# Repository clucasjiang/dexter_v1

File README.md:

# Dexter — Six-Axis Robotic Arm

Dexter is a six-degree-of-freedom robotic arm with a force-controlled gripper, a **PETG-CF 3D-printed structure**, custom controller electronics, and embedded C firmware. The project brings together mechanical design, PCB design, motor communications, and feedback control—from an early prototype to a fully assembled arm that can hold an egg without breaking it.

I designed, built, assembled, programmed, and tested Dexter independently. The stepper-driven arm and the firmware in this repository are the completed, tested first version of an ongoing robotics project. I am now developing a second version with BLDC motors to improve motion quality, control performance, and overall results.

**Core technologies:** KiCad · STM32H562 · Embedded C · RS485 · PID control · Motor current feedback

## Demonstrations

| Gentle grasping | Arm motion |
| --- | --- |
|  |  |
| A PID force loop regulates the grip to hold an egg without breaking it. | A wave demonstration shows the assembled arm in motion. |

The egg demonstration highlights the central controls challenge: applying enough force to retain a delicate object while limiting additional closing motion after contact.

## Mechanical Design

| Early prototype | Fully assembled arm |
| --- | --- |
|  |  |
| An early build used to develop the mechanical arrangement. | The completed assembly integrates the joints, housings, wiring, and gripper. |

- **Printed structure:** PETG-CF (carbon-fiber-filled PETG) forms the arm's structural parts and housings, with metal motors, reducers, bearings, and fasteners integrated into the assembly.
- **Six articulated joints plus a gripper:** Seven addressed motor axes separate arm positioning from grasp-force control.
- **Harmonic reduction:** Reducers transmit motor motion to the joints. J1–J3 use 42 mm motors with 50:1 reduction, and J4–J6 use 35 mm motors with 30:1 reduction.
- **Internal belt-and-pulley transmission:** Belts transfer motion within the links, allowing motors and transmission components to fit inside the printed structure.
- **Portable mechanical deliverable:** The [Dexter STEP assembly](CAD/DexterAssembly.STEP) can be inspected in standard CAD tools.

*Inside the housings: stepper motors, harmonic reduction, and the pulley structure that drives the arm.*

## Electronics

The [KiCad controller project](PCB/main_controller/dexter_pcb.kicad_pro) includes the schematic, PCB layout, component libraries, footprints, and 3D models.

The stepper motors have built-in drivers from **ZDT**, so the STM32 can send movement commands directly over RS485 and read back position, speed, and motor current. Each motor has its own address on the bus.

| Subsystem | Implementation |
| --- | --- |
| Main controller | STM32H562 microcontroller running the arm application and peripheral interfaces. |
| Power | 24 V input through an XT60 connector and an AP63203 regulator for the 3.3 V logic supply. |
| Motor bus | MAX3485 RS485 transceiver; firmware addresses joints as 1–6 and the gripper as 7 at 115200 baud. |
| Grip feedback | The claw motor's built-in phase-current feedback, read over RS485 in milliamps and used as a proxy for grip load. |
| Development interfaces | Debug/programming connections, reset/boot circuitry, and a serial command console. |
| External stop input | PC13 accepts a normally closed emergency-stop loop; an open input requests a stop. This connection is external to the current controller PCB. |

The firmware pin assignments match the controller PCB: PA0/PA1 carry the UART4 motor bus, PA2 controls the MAX3485 transmit enable, and PB5/PB6 provide the UART5 serial console.

## Firmware and Control

The firmware uses a bare-metal C11 application with separate board, protocol, joint-control, gripper-control, and scheduling layers.

### Joint motion and motor feedback

[arm.c](Firmware/App/Src/arm.c) converts joint angles and speeds into motor commands using each joint's reduction and direction. It supports absolute joint moves, configurable travel and speed limits, manual reference capture, explicit arming, and individual or whole-arm stops. Feedback monitoring checks following error, lack of progress, motion deadlines, stale telemetry, and driver faults.

[zdt.c](Firmware/App/Src/zdt.c) implements the ZDT **X-firmware** protocol over RS485, including trapezoidal position moves, current-limited commands, configuration checks, and telemetry decoding. Transactions validate reply framing and acknowledgements, use bounded timeouts, and avoid automatic motion retries. Decoded feedback includes position, speed, following error, current, voltage, temperature, and driver status.

### Force-controlled gripper

[gripper.c](Firmware/App/Src/gripper.c) uses the claw stepper's built-in phase-current feedback as a proxy for grip load. The application polls aggregate status from motor 7 every 20 ms, obtaining current, position, speed, and driver flags together.

The outer PID turns measured phase current into small opening or closing corrections:

1. Ramp the current target gradually to soften initial contact.
2. Filter measured current and its derivative to reduce noise.
3. Apply PID control with derivative on measurement, integral anti-windup, and a current deadband.
4. Accumulate small corrections at the drive's 0.1° resolution, with a maximum requested step of 0.2°.
5. Wait for fresh motor feedback and completion of the previous move before issuing another correction. If a closing step reaches the requested load while stationary before its endpoint, stop the remaining step and read feedback again so the loop can hold or release.

The application dispatches finite, current-limited position moves (`0xCD`), using the drive's internal control loops. Unfiltered current limits, reply freshness, and gripper travel checks remain active while a move is pending. Communication errors, driver faults, or loss of the claw's volatile reference marker stop operation. The installed motors run **X firmware in closed-loop mode**.

Current is a proxy for motor torque and grip load, not a calibrated jaw-force measurement in newtons. Friction, jaw geometry, and direction affect the relationship. `GRIP` takes **milliamps**. The tested configuration uses a 100 mA maximum target, 150 mA drive limit/software trip, 40 mA/s target ramp, and 3 mA deadband. These limits and the PID gains are used by the completed stepper-driven arm, including the gentle grasping demonstration above. Limits live in [robot_config.h](Firmware/App/Inc/robot_config.h), and PID defaults in [gripper.c](Firmware/App/Src/gripper.c).

### Scheduling, diagnostics, and fault handling

- **100 Hz application scheduling target:** Late updates skip missed releases. Blocking motor transactions affect the achieved rate; one arm joint is polled per update.
- **At most 50 Hz PID corrections:** A 20 ms minimum interval, fresh samples, and motor completion determine the actual correction rate.
- **500 ms nominal independent watchdog:** Refreshed only after a completed application update. Startup requests motor stops and leaves motion disarmed.
- **Observable runtime:** `STATUS` reports joint positions and targets, claw phase current and target in mA, feedback validity and age, faults, measured loop frequency, missed releases, longest update, and watchdog-reset status.
- **Buffered serial console:** Interrupt-driven receive/transmit queues keep console traffic separate from command processing; damaged or oversized input lines are discarded.

Current application motion is joint-space control with manual referencing; Cartesian inverse kinematics, automatic homing, and coordinated trajectory planning are not implemented.

## Build and Explore

Start with the [Dexter STEP assembly](CAD/DexterAssembly.STEP) for the mechanism, the [KiCad schematic](PCB/main_controller/dexter_pcb.kicad_sch) for electronics, and [robot_app.c](Firmware/App/Src/robot_app.c) for application behavior.

### Build the firmware

Requires CMake 3.22+, Ninja, and the GNU Arm Embedded toolchain (`arm-none-eabi-*`) on `PATH`. From the repository root:

```sh
cd Firmware
cmake --preset Debug
cmake --build --preset Debug
```

Outputs are `build/Debug/dexter_legacy.elf`, `.hex`, and `.bin`. A `Release` preset is also provided. [dexter_legacy.ioc](Firmware/dexter_legacy.ioc) contains the STM32CubeMX project configuration.

### Run host tests

The tests run on a computer without connecting the arm. With CMake and a native C compiler, run from the repository root:

```sh
cmake -S Firmware/tests -B Firmware/build/host-tests
cmake --build Firmware/build/host-tests --config Debug
ctest --test-dir Firmware/build/host-tests -C Debug --output-on-failure
```

The claw tests check that it closes when current is low, opens when current is high, and stops on too much current or old feedback. There are also tests for the motor protocol and loop timing. The full firmware has also been tested on the assembled arm; the demonstrations at the top of this page show the resulting motion and grip control.

### Serial operation

Connect a 3.3 V serial adapter to the console at **115200 baud, 8N1**. Commands are uppercase and newline-terminated.

| Command | Purpose |
| --- | --- |
| `HELP`, `STATUS` | Show commands or runtime diagnostics. |
| `ZERO`, `ARM` | Capture the manually positioned zero pose, then permit motion. Place the gripper fully open before `ZERO`. |
| `MOVE joint degrees deg/s` | Move one joint to an absolute angle relative to the captured zero. |
| `GRIP milliamps`, `OPEN` | Regulate measured motor phase current (default range: greater than 0 through 100 mA), or return the gripper to its open reference. |
| `DEMO` | From the zero pose, move each joint sequentially to 5° and back at 2°/s. This is a commissioning routine separate from the wave GIF. |
| `STOP [joint]`, `DISARM`, `CLEAR` | Stop all axes or one axis (1–7), stop and disarm, or clear a fault while disarmed. |

After placing the joints at zero and the claw fully open, use `ZERO`, then `ARM`, then select a tested `GRIP` target in mA. The position reference is lost on reset. Stop commands preserve motor enable where possible, but software stops and the MCU watchdog cannot guarantee holding torque after power or communication loss; gravity-loaded joints need physical support during commissioning.

## Repository Map

| Path | Contents |
| --- | --- |
| [CAD/](CAD/) | Portable STEP assembly of the complete mechanism. |
| [PCB/main_controller/](PCB/main_controller/) | KiCad controller design and supporting libraries. |
| [Firmware/App/](Firmware/App/) | Motor protocol, arm and gripper controllers, command interface, and scheduler. |
| [Firmware/Board/](Firmware/Board/) | UART/RS485, external stop-input, and watchdog interfaces. |
| [Firmware/Core/](Firmware/Core/) | STM32 startup and system initialization; vendor support resides in `Firmware/Drivers/`. |
| [Firmware/tests/](Firmware/tests/) | C tests for the motor protocol, claw control, and loop timing. |
| [README/](README/) | Demonstration GIFs and photographs of the design process and assembly. |

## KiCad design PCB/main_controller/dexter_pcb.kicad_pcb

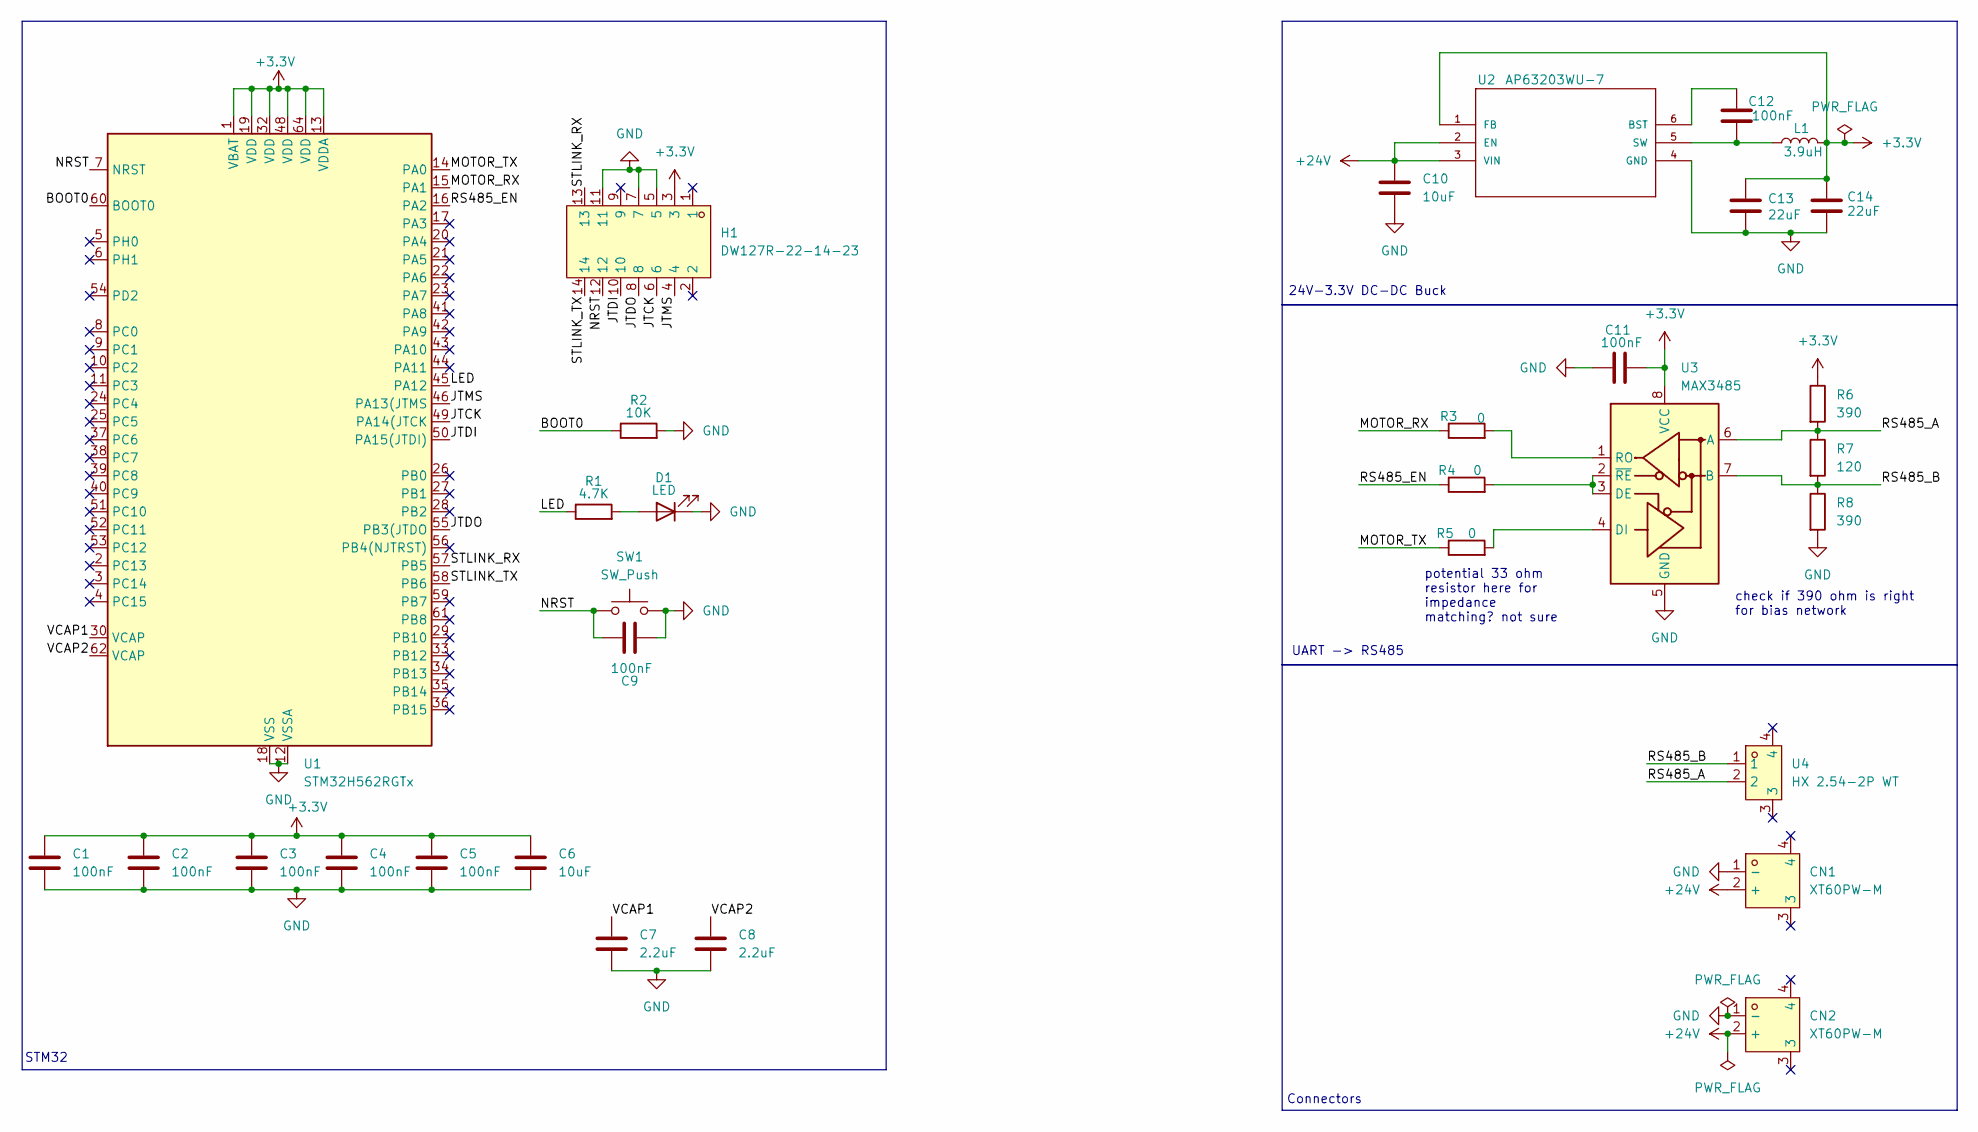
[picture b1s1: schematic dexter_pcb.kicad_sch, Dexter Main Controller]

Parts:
C1, C2, C3, C4, C5, C9, C11, C12: 100nF; C_0603_1608Metric_Pad1.08x0.95mm_HandSolder
C6, C10: 10uF; C_0603_1608Metric_Pad1.08x0.95mm_HandSolder
C7, C8: 2.2uF; C_0603_1608Metric_Pad1.08x0.95mm_HandSolder
C13, C14: 22uF; C_0603_1608Metric_Pad1.08x0.95mm_HandSolder
CN1, CN2: XT60PW-M; CONN-TH_XT60PW-M; MPN XT60PW-M; LCSC Part C98732
D1: LED; LED_0603_1608Metric_Pad1.05x0.95mm_HandSolder
H1: DW127R-22-14-23; HDR-TH_14P-P1.27-V-M-R2-C7-S1.27-2; MPN DW127R-22-14-23; LCSC Part C2935955
L1: 3.9uH; L_Changjiang_FNR4030S; LCSC C167872
R1: 4.7K; R_0603_1608Metric_Pad0.98x0.95mm_HandSolder
R2: 10K; R_0603_1608Metric_Pad0.98x0.95mm_HandSolder
R3, R4, R5: 0; R_0603_1608Metric_Pad0.98x0.95mm_HandSolder
R6, R8: 390; R_0603_1608Metric_Pad0.98x0.95mm_HandSolder
R7: 120; R_0603_1608Metric_Pad0.98x0.95mm_HandSolder
SW1: SW_Push; SW_SPST_TS-1088-xR020; LCSC C720477
U1: STM32H562RGTx; LQFP-64_10x10mm_P0.5mm; LCSC C19711662
U2: AP63203WU-7; TSOT-23-6_HandSoldering; MPN AP63203WU-7; LCSC C780769
U3: MAX3485; SOIC-8_3.9x4.9mm_P1.27mm; LCSC C9943
U4: HX 2.54-2P WT; CONN-SMD_2P-P2.54-XH2.54-WT; MPN HX 2.54-2P WT; LCSC Part C5142098

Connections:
+3.3V: C1.1, C2.1, C3.1, C4.1, C5.1, C6.1, C11.2, C13.1, C14.1, H1.3, L1.2, R6.1, U1.1 (VBAT), U1.13 (VDDA), U1.19 (VDD), U1.32 (VDD), U1.48 (VDD), U1.64 (VDD), U2.1 (FB), U3.8 (VCC)
+24V: C10.1, CN1.2 (+), CN2.2 (+), U2.2 (EN), U2.3 (VIN)
/BOOT0: R2.1, U1.60 (BOOT0)
/JTCK: H1.6, U1.49 (PA14(JTCK)
/JTDI: H1.10, U1.50 (PA15(JTDI))
/JTDO: H1.8, U1.55 (PB3(JTDO)
/JTMS: H1.4, U1.46 (PA13(JTMS)
/LED: R1.1, U1.45 (PA12)
/MOTOR_RX: R3.1, U1.15 (PA1)
/MOTOR_TX: R5.1, U1.14 (PA0)
/NRST: C9.1, H1.12, SW1.1, U1.7 (NRST)
/RS485_A: R6.2, R7.1, U3.6 (A), U4.2
/RS485_B: R7.2, R8.1, U3.7 (B), U4.1
/RS485_EN: R4.1, U1.16 (PA2)
/STLINK_RX: H1.13, U1.57 (PB5)
/STLINK_TX: H1.14, U1.58 (PB6)
/VCAP1: C7.1, U1.30 (VCAP)
/VCAP2: C8.1, U1.62 (VCAP)
GND: C1.2, C2.2, C3.2, C4.2, C5.2, C6.2, C7.2, C8.2, C9.2, C10.2, C11.1, C13.2, C14.2, CN1.1 (-), CN2.1 (-), D1.1 (K), H1.5, H1.7, H1.11, R2.2, R8.2, SW1.2, U1.12 (VSSA), U1.18 (VSS), U1.31 (VSS), U1.47 (VSS), U1.63 (VSS), U2.4 (GND), U3.5 (GND)
unnamed: D1.2 (A), R1.2
unnamed: C12.1, U2.6 (BST)
unnamed: C12.2, L1.1, U2.5 (SW)
unnamed: R4.2, U3.2 (~RE), U3.3 (DE)
unnamed: R5.2, U3.4 (DI)
unnamed: R3.2, U3.1 (RO)

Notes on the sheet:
UART -> RS485
24V-3.3V DC-DC Buck
STM32
Connectors
check if 390 ohm is right for bias network
potential 33 ohm resistor here for impedance matching? not sure

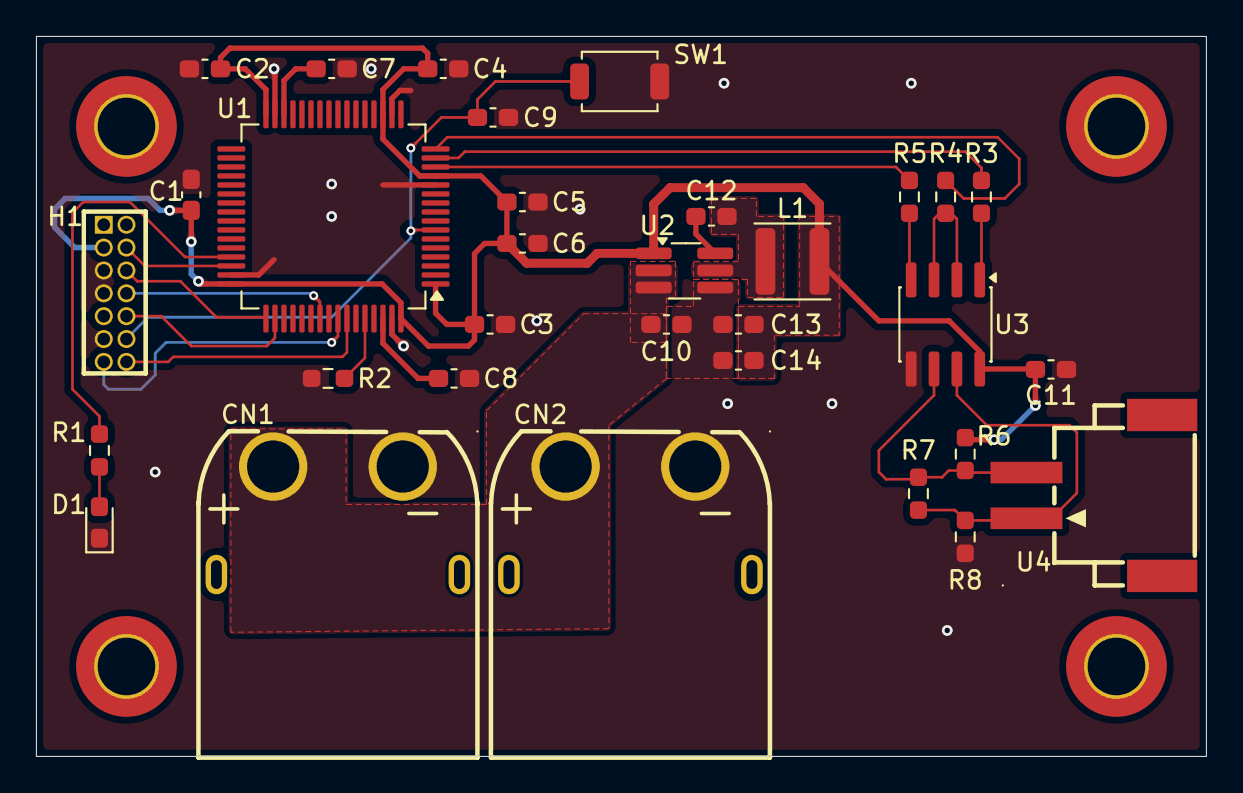
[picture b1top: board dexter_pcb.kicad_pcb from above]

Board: 2 copper layers, 65.0 x 40.0 mm, 32 parts (0 on the bottom side), 25 nets.

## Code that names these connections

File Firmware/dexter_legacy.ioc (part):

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Mcu.Name=STM32H562RGTx
Mcu.Package=LQFP64
Mcu.UserName=STM32H562RGTx
PA13(JTMS/SWDIO).Mode=JTAG_5_pins
PA13(JTMS/SWDIO).Signal=DEBUG_JTMS-SWDIO
PA14(JTCK/SWCLK).Mode=JTAG_5_pins
PA14(JTCK/SWCLK).Signal=DEBUG_JTCK-SWCLK
PA15(JTDI).Mode=JTAG_5_pins
PA15(JTDI).Signal=DEBUG_JTDI
PB3(JTDO/TRACESWO).Mode=JTAG_5_pins
PB3(JTDO/TRACESWO).Signal=DEBUG_JTDO-SWO
PB4(NJTRST).Mode=JTAG_5_pins
PB4(NJTRST).Signal=DEBUG_NJTRST
RCC.HSE_VALUE=25000000
RCC.SYSCLKFreq_VALUE=32000000
board=custom

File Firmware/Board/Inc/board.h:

#ifndef BOARD_H
#define BOARD_H

#include <stdbool.h>
#include <stddef.h>
#include <stdint.h>

#define BOARD_WATCHDOG_TIMEOUT_MS 500U

/* Pin assignments for the Dexter STM32H562RGT6 controller PCB:
 * PA0 / PA1: UART4 TX / RX to MAX3485 DI / RO, AF8, 115200 baud, 8N1.
 * PA2: MAX3485 DE and /RE tied together (high = transmit).
 * PB5 / PB6: UART5 RX / TX, AF14, 115200 baud, 3.3 V serial console.
 * PC13: external normally closed emergency-stop loop to GND; open/high = stop.
 * All external logic must be 3.3 V compatible.
 */

/* Call after HAL_Init() and SystemClock_Config(), with interrupts enabled. */
bool board_init(void);
uint32_t board_millis(void);

/* One request and one exact-length reply. No retry: a failed command may have
 * reached the motor already. The application decides how to handle failures.
 * rx_len == 0 permits a broadcast with no reply. Maximum frame size is 64.
 * The entire operation is bounded by timeout_ms, limited to 10 ms here.
 * Configure ZDT Response=Receive so arrival notifications cannot mix with replies.
 */
bool board_motor_exchange(const uint8_t *tx, size_t tx_len,
                          uint8_t *rx, size_t rx_len, uint32_t timeout_ms);

/* Console RX/TX use interrupt rings so motor polling does not lose commands.
 * RX corruption/overflow returns ASCII CAN (0x18): discard the current command
 * through its next newline. TX is best effort; a full queue drops a whole write.
 */
bool board_console_read(char *ch);
void board_console_write(const char *text);

bool board_estop_active(void);
/* Start immediately after HAL_Init(), before configuring clocks/peripherals.
 * Timeout is nominal: the independent LSI oscillator has frequency tolerance.
 */
bool board_watchdog_init(void);
bool board_watchdog_was_reset(void);
/* Call only after a complete main-loop update. Never feed from an ISR/wait. */
void board_watchdog_refresh(void);

#endif
